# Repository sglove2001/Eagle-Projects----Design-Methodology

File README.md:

# Eagle-Projects----Design-Methodology
Eagle Schematics for download/import, include libraries used and all schematics/boards

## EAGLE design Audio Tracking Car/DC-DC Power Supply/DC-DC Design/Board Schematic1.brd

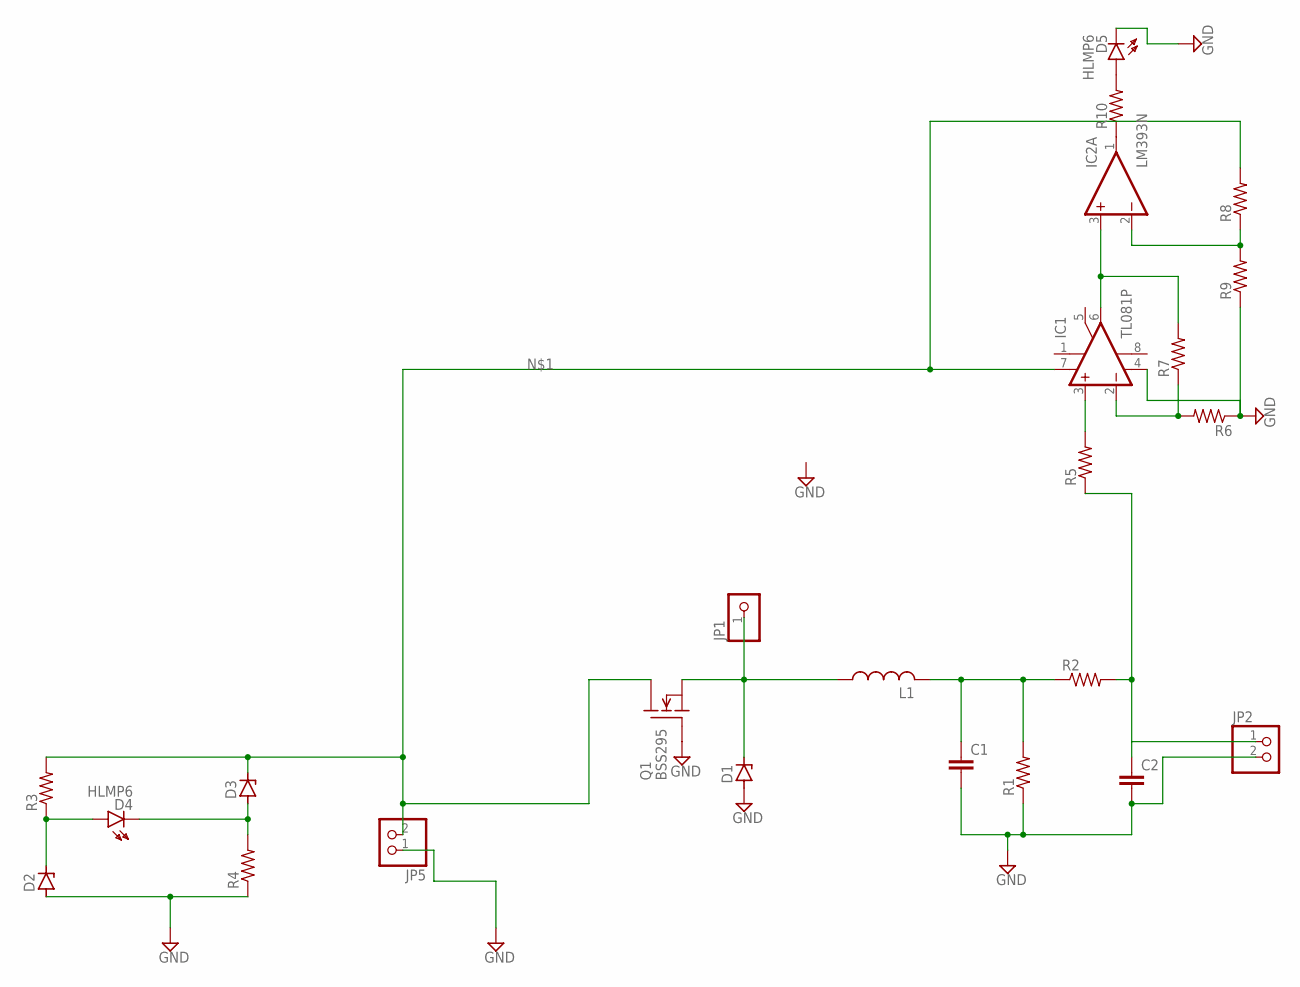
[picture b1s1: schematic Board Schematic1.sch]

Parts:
C1, C2: C-EU025-025X050; C025-025X050
D1, D2, D3: ZENER-DIODEDO35Z10; DO35Z10
D4, D5: HLMP6
IC1: TL081P; DIL08
IC2: LM393N; DIL08
JP1: PINHD-1X1; 1X01
JP2, JP5: PINHD-1X2; 1X02
L1: L-US6000-XXX-RC; 6000-XXXX-RC
Q1: BSS295; TO92
R1, R2, R3, R4, R5, R6, R7, R8, R9, R10: R-US_0204/7; 0204/7

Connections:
GND: C1.2, C2.2, D1.A, D2.A, D5.K, IC1.4 (V-), JP2.2, JP5.1, Q1.1 (G), R1.1, R4.1, R6.1, R9.1
unnamed: D3.C, IC1.7 (V+), JP5.2, Q1.2 (D), R3.2, R8.2
unnamed: D1.C, JP1.1, L1.1, Q1.3 (S)
unnamed: C1.1, L1.2, R1.2, R2.1
unnamed: C2.1, JP2.1, R2.2, R5.1
unnamed: IC1.3 (+IN), R5.2
unnamed: D2.C, D4.A, R3.1
unnamed: D3.A, D4.K, R4.2
unnamed: IC1.2 (-IN), R6.2, R7.1
unnamed: IC1.6 (OUT), IC2.3 (+IN), R7.2
unnamed: IC2.2 (-IN), R8.1, R9.2
unnamed: D5.A, R10.2
unnamed: IC2.1 (OUT), R10.1
V+: IC2.8 (V+)
V-: IC2.4 (V-)

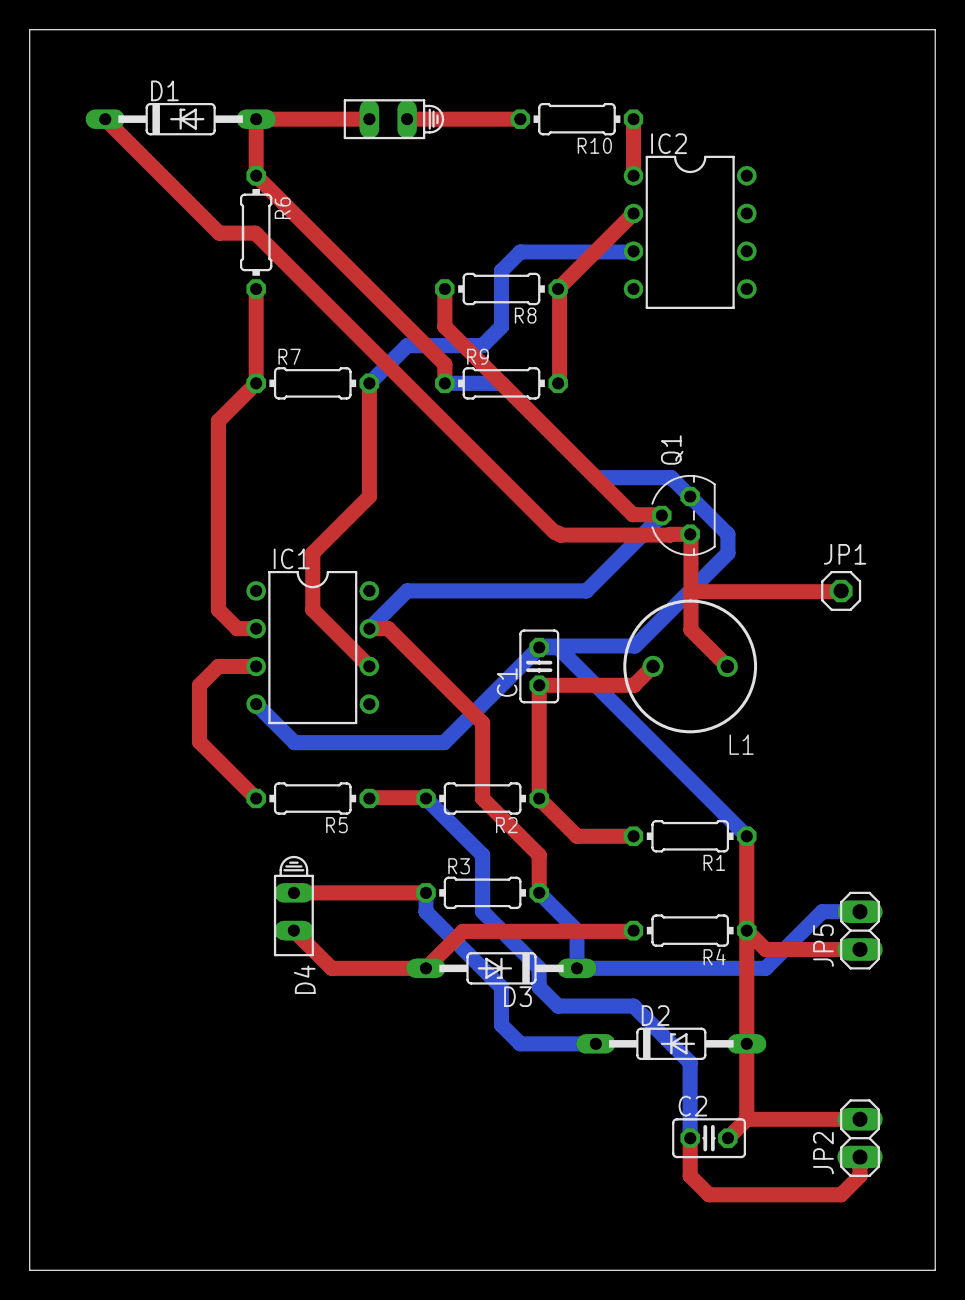
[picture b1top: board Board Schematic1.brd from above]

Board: 2 copper layers, 60.9 x 83.5 mm, 24 parts (0 on the bottom side), 13 nets.

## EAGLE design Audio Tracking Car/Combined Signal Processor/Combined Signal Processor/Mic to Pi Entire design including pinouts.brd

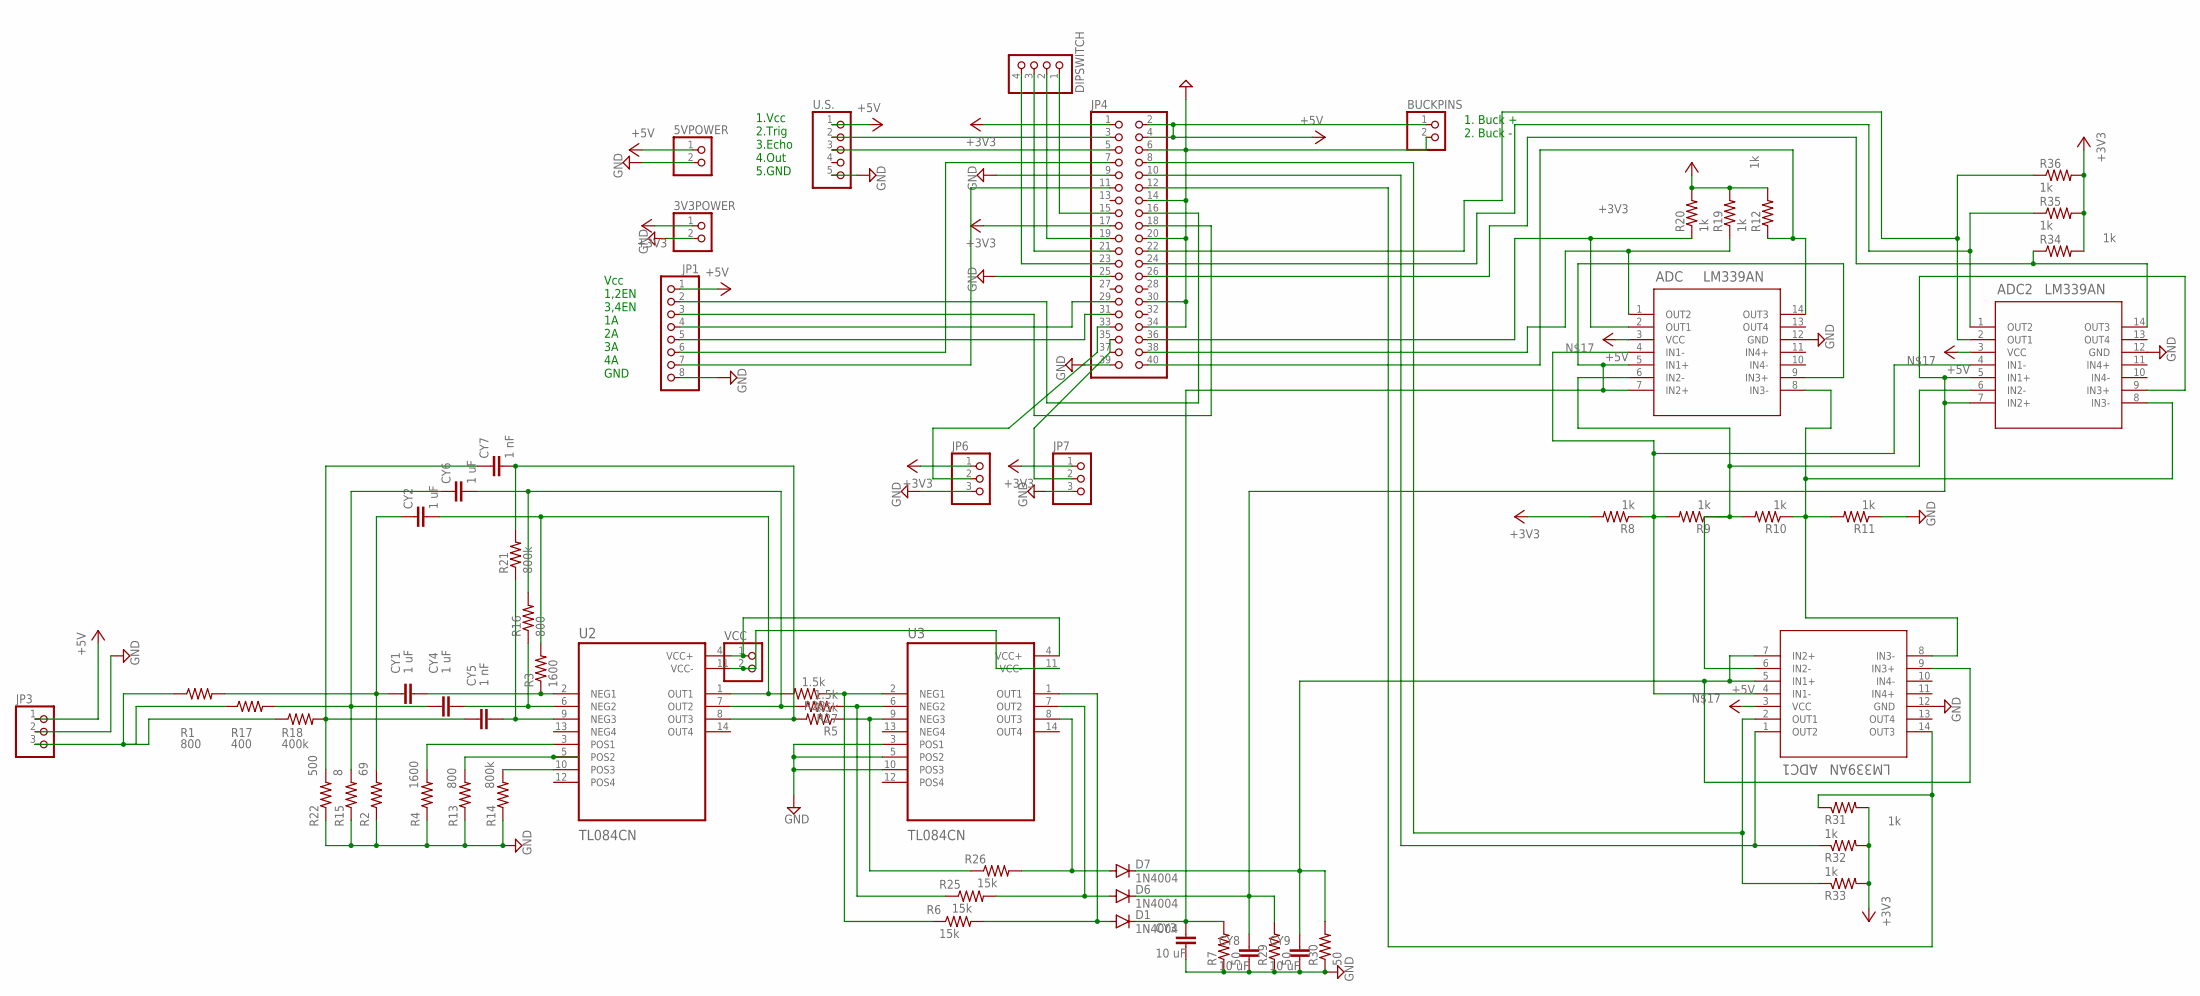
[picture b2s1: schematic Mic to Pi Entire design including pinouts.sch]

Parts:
3V3POWER, 5VPOWER: PINHD-1X2; 1X02
ADC, ADC1, ADC2: LM339AN; PDIP14_646-06_ONS
BUCKPINS: PINHD-1X2; 1X02
CY1, CY2, CY4, CY6: 1 uF; YC7B5
CY3, CY8, CY9: 10 uF; YC7B5
CY5, CY7: 1 nF; YC7B5
D1, D6, D7: 1N4004; DO41-10
DIPSWITCH: PINHD-1X4; 1X04
JP1: PINHD-1X8; 1X08
JP3, JP6, JP7: PINHD-1X3; 1X03
JP4: PINHD-2X20; 2X20
R1, R13, R16: 800; 0204/7
R2: 69; 0204/7
R3, R4: 1600; 0204/7
R5, R27, R28: 1.5k; 0204/7
R6, R25, R26: 15k; 0204/7
R7, R29, R30: 50; 0204/7
R8, R19, R20, R32, R33, R35, R36: 1k; 0204/7
R9, R10, R11, R12, R31, R34: 1k; 0207/2V
R14, R21: 800k; 0204/7
R15: 8; 0204/7
R17: 400; 0204/7
R18: 400k; 0204/7
R22: 500; 0204/7
U2, U3: TL084CN; DIP794W45P254L1969H508Q14
U.S.: PINHD-1X55X2MM; 1_05X2MM
VCC: PINHD-1X2; 1X02

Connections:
+3V3: 3V3POWER.1, JP4.1, JP4.17, JP6.1, JP7.1, R8.2, R12.2, R19.2, R20.2, R31.2, R32.2, R33.2, R34.2, R35.2, R36.2
+5V: 5VPOWER.1, ADC.3 (VCC), ADC1.3 (VCC), ADC2.3 (VCC), BUCKPINS.1, JP1.1, JP3.1, JP4.2, JP4.4, U.S..1
GND: 3V3POWER.2, 5VPOWER.2, ADC.12 (GND), ADC1.12 (GND), ADC2.12 (GND), BUCKPINS.2, CY3.2, CY8.2, CY9.2, JP1.8, JP3.2, JP4.6, JP4.9, JP4.14, JP4.20, JP4.25, JP4.30, JP4.34, JP4.39, JP6.3, JP7.3, R2.1, R4.1, R7.1, R11.1, R13.1, R14.1, R15.1, R22.1, R29.1, R30.1, U3.3 (POS1), U3.5 (POS2), U3.10 (POS3), U.S..5
unnamed: R6.1, R28.1, U3.2 (NEG1)
unnamed: R13.2, U2.5 (POS2)
unnamed: R14.2, U2.10 (POS3)
unnamed: JP3.3, R1.1, R17.1, R18.1
unnamed: CY4.1, CY6.1, R15.2, R17.2
unnamed: CY5.1, CY7.1, R18.2, R22.2
unnamed: CY4.2, R16.1, U2.6 (NEG2)
unnamed: CY2.2, R3.2, R28.2, U2.1 (OUT1)
unnamed: CY5.2, R21.1, U2.9 (NEG3)
unnamed: CY6.2, R16.2, R27.2, U2.7 (OUT2)
unnamed: CY1.1, CY2.1, R1.2, R2.2
unnamed: CY1.2, R3.1, U2.2 (NEG1)
unnamed: R4.2, U2.3 (POS1)
unnamed: CY7.2, R5.2, R21.2, U2.8 (OUT3)
unnamed: ADC.5 (IN1+), ADC.7 (IN2+), ADC.9 (IN3+), CY3.1, D1.C, R7.2
unnamed: ADC.1 (OUT2), JP4.38, R19.1
unnamed: ADC.4 (IN1-), ADC1.4 (IN1-), ADC2.4 (IN1-), R8.1, R9.2
unnamed: ADC.6 (IN2-), ADC1.6 (IN2-), ADC2.6 (IN2-), R9.1, R10.2
unnamed: ADC.8 (IN3-), ADC1.8 (IN3-), ADC2.8 (IN3-), R10.1, R11.2
unnamed: ADC.2 (OUT1), JP4.36, R20.1
unnamed: ADC.14 (OUT3), JP4.40, R12.1
unnamed: JP4.3, U.S..2
unnamed: JP4.5, U.S..3
unnamed: R25.1, R27.1, U3.6 (NEG2)
unnamed: D1.A, R6.2, U3.1 (OUT1)
unnamed: R5.1, R26.1, U3.9 (NEG3)
unnamed: D7.A, R26.2, U3.8 (OUT3)
unnamed: JP1.4, JP4.29
unnamed: JP1.5, JP4.31
unnamed: JP1.6, JP4.7
unnamed: JP1.7, JP4.11
unnamed: JP1.2, JP4.16
unnamed: JP1.3, JP4.18
unnamed: DIPSWITCH.1, JP4.15
unnamed: DIPSWITCH.2, JP4.19
unnamed: DIPSWITCH.3, JP4.21
unnamed: DIPSWITCH.4, JP4.23
unnamed: JP4.33, JP6.2
unnamed: JP4.35, JP4.37, JP7.2
unnamed: U2.11 (VCC-), U3.11 (VCC-), VCC.2
unnamed: U2.4 (VCC+), U3.4 (VCC+), VCC.1
unnamed: D6.A, R25.2, U3.7 (OUT2)
unnamed: ADC2.5 (IN1+), ADC2.7 (IN2+), ADC2.9 (IN3+), CY8.1, D6.C, R29.2
unnamed: ADC1.5 (IN1+), ADC1.7 (IN2+), ADC1.9 (IN3+), CY9.1, D7.C, R30.2
unnamed: ADC1.1 (OUT2), JP4.10, R32.1
unnamed: ADC1.14 (OUT3), JP4.12, R31.1
unnamed: ADC1.2 (OUT1), JP4.8, R33.1
unnamed: ADC2.1 (OUT2), JP4.24, R35.1
unnamed: ADC2.14 (OUT3), JP4.26, R34.1
unnamed: ADC2.2 (OUT1), JP4.22, R36.1

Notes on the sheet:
1. Buck + 2. Buck -
1.Vcc 2.Trig 3.Echo 4.Out 5.GND
Vcc 1,2EN 3,4EN 1A 2A 3A 4A GND

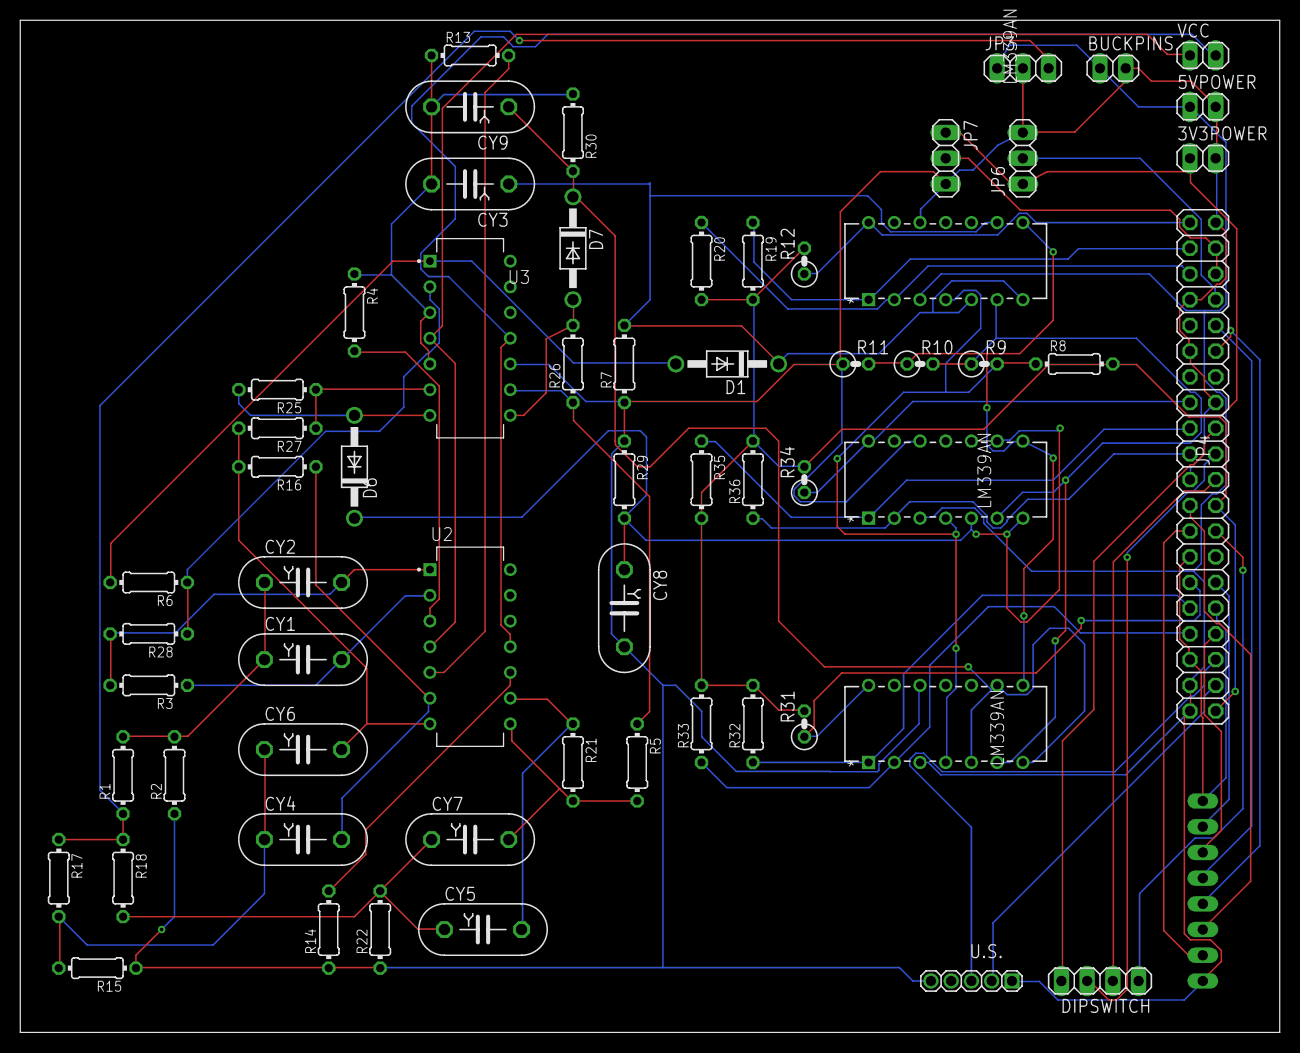
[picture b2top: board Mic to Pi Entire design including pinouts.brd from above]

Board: 2 copper layers, 124.4 x 100.0 mm, 62 parts (1 on the bottom side), 53 nets.

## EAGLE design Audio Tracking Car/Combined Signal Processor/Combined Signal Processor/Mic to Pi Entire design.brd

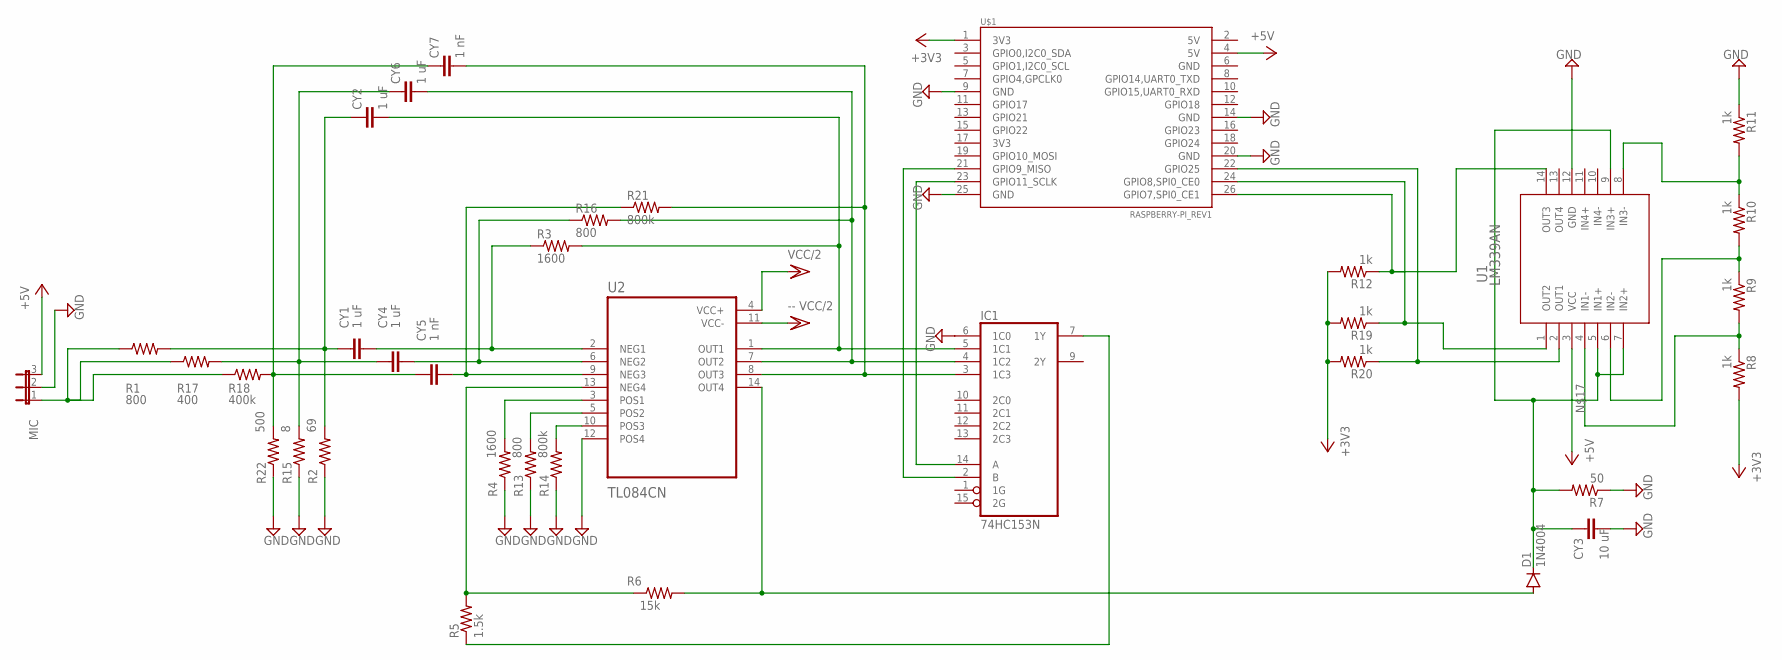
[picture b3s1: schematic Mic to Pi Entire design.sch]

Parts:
CY1, CY2, CY4, CY6: 1 uF; YC7B5
CY3: 10 uF; YC7B5
CY5, CY7: 1 nF; YC7B5
D1: 1N4004; DO41-10
IC1: 74HC153N; DIL16
MIC: JP2W
R1, R13, R16: 800; 0204/7
R2: 69; 0204/7
R3, R4: 1600; 0204/7
R5: 1.5k; 0204/7
R6: 15k; 0204/7
R7: 50; 0204/7
R8, R19, R20: 1k; 0204/7
R9, R10, R11, R12: 1k; 0207/2V
R14, R21: 800k; 0204/7
R15: 8; 0204/7
R17: 400; 0204/7
R18: 400k; 0204/7
R22: 500; 0204/7
U1: LM339AN; PDIP14_646-06_ONS
U2: TL084CN; DIP794W45P254L1969H508Q14
U$1: RASPBERRY-PI_REV1

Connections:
+3V3: R8.2, R12.2, R19.2, R20.2, U$1.1 (3V3); also elsewhere on the board
+5V: MIC.3, U1.3 (VCC), U$1.4 (5V); also elsewhere on the board
GND: CY3.2, IC1.6 (1C0), MIC.2, R2.1, R4.1, R7.1, R11.1, R13.1, R14.1, R15.1, R22.1, U1.12 (GND), U2.12 (POS4), U$1.9 (GND), U$1.14 (GND), U$1.20 (GND), U$1.25 (GND); also elsewhere on the board
unnamed 3: IC1.7 (1Y), R5.1; also elsewhere on the board
unnamed: R13.2, U2.5 (POS2)
unnamed: R14.2, U2.10 (POS3)
unnamed 6: MIC.1, R1.1, R17.1, R18.1; also elsewhere on the board
unnamed: CY4.1, CY6.1, R15.2, R17.2
unnamed: CY5.1, CY7.1, R18.2, R22.2
unnamed: CY4.2, R16.1, U2.6 (NEG2)
unnamed 10: CY2.2, IC1.5 (1C1), R3.2, U2.1 (OUT1); also elsewhere on the board
unnamed: CY5.2, R21.1, U2.9 (NEG3)
unnamed 12: CY6.2, IC1.4 (1C2), R16.2, U2.7 (OUT2); also elsewhere on the board
unnamed: CY1.1, CY2.1, R1.2, R2.2
unnamed: CY1.2, R3.1, U2.2 (NEG1)
unnamed: R4.2, U2.3 (POS1)
unnamed 16: CY7.2, IC1.3 (1C3), R21.2, U2.8 (OUT3); also elsewhere on the board
unnamed: CY3.1, D1.C, R7.2, U1.5 (IN1+), U1.7 (IN2+), U1.9 (IN3+)
unnamed: R19.1, U1.1 (OUT2), U$1.24 (GPIO8,SPI0_CE0)
unnamed: R8.1, R9.2, U1.4 (IN1-)
unnamed: R9.1, R10.2, U1.6 (IN2-)
unnamed: R10.1, R11.2, U1.8 (IN3-)
unnamed: R20.1, U1.2 (OUT1), U$1.22 (GPIO25)
unnamed: R12.1, U1.14 (OUT3), U$1.26 (GPIO7,SPI0_CE1)
unnamed: R5.2, R6.1, U2.13 (NEG4)
unnamed: D1.A, R6.2, U2.14 (OUT4)
unnamed 26: IC1.2 (B), U$1.21 (GPIO9_MISO); also elsewhere on the board
unnamed 27: IC1.14 (A), U$1.23 (GPIO11_SCLK); also elsewhere on the board
VCC/2: U2.4 (VCC+), U2.11 (VCC-)

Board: 2 copper layers, 36 parts (0 on the bottom side), 29 nets, no tracks yet.

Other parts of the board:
SV1: MA17-2
SV2: MA03-1
U3: SN74LS153N; DIP794W45P254L1969H508Q16

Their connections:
+3V3: U3.16; also elsewhere on the board
+5V: SV2.3; also elsewhere on the board
GND: SV2.2, U3.6, U3.8; also elsewhere on the board
unnamed 3: U3.7; also elsewhere on the board
unnamed 6: SV2.1; also elsewhere on the board
unnamed 10: U3.5; also elsewhere on the board
unnamed 12: U3.4; also elsewhere on the board
unnamed 16: U3.3; also elsewhere on the board
unnamed 26: U3.2; also elsewhere on the board
unnamed 27: U3.14; also elsewhere on the board

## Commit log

2022-03-26 Initial Eagle Schematic push
2022-03-26 Material List for deliverable 10
2022-03-29 complete design 1.0.1
2022-03-30 Added pins to Vcc v.1.0.2
2022-03-30 Add files via upload
    DC-DC design for progress deliverable
2022-04-04 Included multiple versions
2022-04-04 missing connection fix
2022-04-05 Fixed Diodes
2022-04-05 new brd
2022-04-05 new new

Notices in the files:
parts and their libraries:
COPYRIGHT: Copyright (C) 2022 Ultra Librarian. All rights reserved.
